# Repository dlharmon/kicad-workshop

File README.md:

# kicad-workshop
Material for a Kicad workshop

## Overview

A three session workshop on designing and assembling PCBs with
Kicad. A small group of students will design and build a USB
widget. The instructor will provide the basic circuit and
guidance. Materials cost will be approximately $20 including PCB
fabrication, components, shipping and solder paste stencil. We will
place a shared order to reduce shipping costs.

## [Slides](https://raw.githubusercontent.com/dlharmon/kicad-workshop/master/slides/kicad-workshop.pdf)

## The device

- [Silicon Labs EFM32HG309 microcontroller](https://www.silabs.com/products/mcu/32-bit/efm32-happy-gecko), ARM Cortex M0+, 64 kiB flash, 8 kiB ram USB device interface. About $1.50.
 - Connector for [128x64 pixel OLED](https://www.aliexpress.com/item/32847040077.html?spm=a2g0s.9042311.0.0.6e644c4dlFzZIQ) Display is not included in the parts kit, order one yourself if you want it.
 - LEDs
 - rotary encoder with push switch
 - USB for power and communication, will provide Python code to communicate with it from a PC
 - This is about $3 in parts yet demonstrates quite a few things

## Prerequisites
 - Laptop with [Kicad 5.1.4](http://www.kicad.org/download/) 5.1.2 is probably OK. Last time we had a few students using 5.0.x and it was problematic.
 - [Interactive HTML BOM plugin installed](https://github.com/openscopeproject/InteractiveHtmlBom) (optional, may require installing python3-wxgtk4)
 - Electronics knowledge is not required, but helpful.
 - Programming knowledge is not required, but helpful.
 - USB C cable (C-C for newer laptops, A-C for older) by last session. I'll have a few on hand.
 - Clone or download [https://github.com/sethhillbrand/kicad_templates.git](https://github.com/sethhillbrand/kicad_templates.git)

## Firmware
 - This is entirely optional. The instructor can flash firmware for you if you are not interested.
 - [ARM Cortex compiler](https://developer.arm.com/tools-and-software/open-source-software/developer-tools/gnu-toolchain/gnu-rm/downloads) Alternately, your Linux distro may have a package `gcc-arm-none-eabi` or similar which may work.
 - [OpenOCD](http://openocd.org/) required to flash the firmware the first time and until a bootloader is developed.
 - In the fw directory, `make flash` will build and flash the firmware. It assumes an FT232H based programmer with the default USB ID.
 - usb_comm.py can be used to interact with the device from Python over USB.

### udev rules

On Linux, to avoid having to run as root (change dlharmon to your user), add the following to `/etc/udev/rules.d/99-local.rules`:

```
ATTR{idVendor}=="0403", ATTR{idProduct}=="6014", SYMLINK+="ftdi-%k", MODE="660", GROUP="dlharmon"
SUBSYSTEM=="usb", ATTR{idVendor}=="10c4", ATTR{idProduct}=="8b00", MODE="0660", GROUP="dlharmon"
```

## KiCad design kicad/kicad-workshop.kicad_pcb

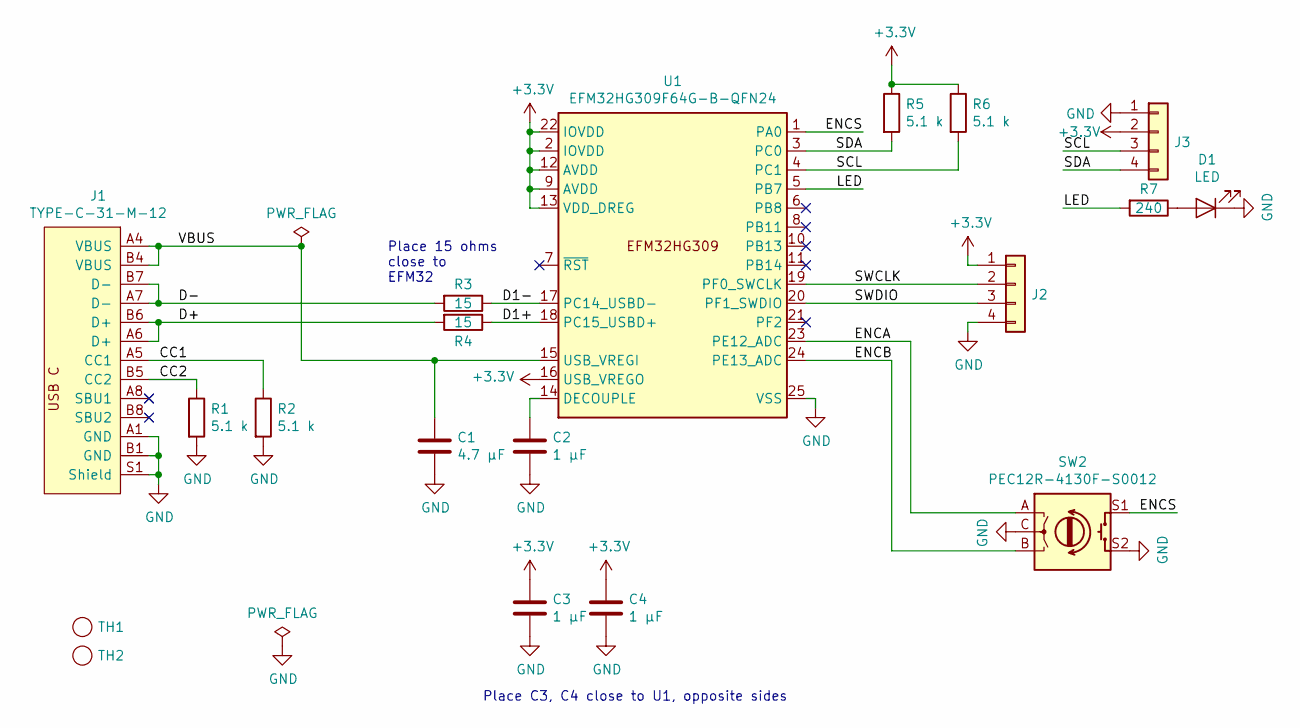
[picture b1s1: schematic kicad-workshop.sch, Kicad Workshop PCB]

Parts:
C1: 4.7 μF; C_0603_1608Metric
C2, C3, C4: 1 μF; C_0603_1608Metric
D1: LED; LED_0603_1608Metric
J1: TYPE-C-31-M-12; USB_C_Receptacle_HRO_TYPE-C-31-M-12
J2: Conn_01x04; PinHeader_1x04_P2.54mm_Vertical
J3: Conn_01x04; PinSocket_1x04_P2.54mm_Vertical
R1, R2, R5, R6: 5.1 k; R_0603_1608Metric
R3, R4: 15; R_0603_1608Metric
R7: 240; R_0603_1608Metric
SW2: PEC12R-4130F-S0012; RotaryEncoder_Alps_EC12E-Switch_Vertical_H20mm
TH1, TH2: tooling_hole; tooling_hole_2.55
U1: EFM32HG309F64G-B-QFN24; QFN-24-1EP_5x5mm_P0.65mm_EP3.6x3.6mm

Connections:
+3V3: C3.1, C4.1, J2.1, J3.2, R5.1, R6.1, U1.2 (IOVDD), U1.9 (AVDD), U1.12 (AVDD), U1.13 (VDD_DREG), U1.16 (USB_VREGO), U1.22 (IOVDD)
/CC1: J1.A5 (CC1), R2.1
/CC2: J1.B5 (CC2), R1.1
/D1+: R4.1, U1.18 (PC15_USBD+)
/D1-: R3.1, U1.17 (PC14_USBD-)
/D+: J1.A6 (D+), J1.B6 (D+), R4.2
/D-: J1.A7 (D-), J1.B7 (D-), R3.2
/ENCA: SW2.A, U1.23 (PE12_ADC)
/ENCB: SW2.B, U1.24 (PE13_ADC)
/ENCS: SW2.S1, U1.1 (PA0)
/LED: R7.2, U1.5 (PB7)
/SCL: J3.3, R6.2, U1.4 (PC1)
/SDA: J3.4, R5.2, U1.3 (PC0)
/SWCLK: J2.2, U1.19 (PF0_SWCLK)
/SWDIO: J2.3, U1.20 (PF1_SWDIO)
/VBUS: C1.1, J1.A4 (VBUS), J1.B4 (VBUS), U1.15 (USB_VREGI)
GND: C1.2, C2.2, C3.2, C4.2, D1.1 (K), J1.A1 (GND), J1.B1 (GND), J1.S1 (Shield), J2.4, J3.1, R1.2, R2.2, SW2.C, SW2.S2, U1.25 (VSS)
unnamed: C2.1, U1.14 (DECOUPLE)
unnamed: D1.2 (A), R7.1

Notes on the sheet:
Place 15 ohms close to EFM32
Place C3, C4 close to U1, opposite sides

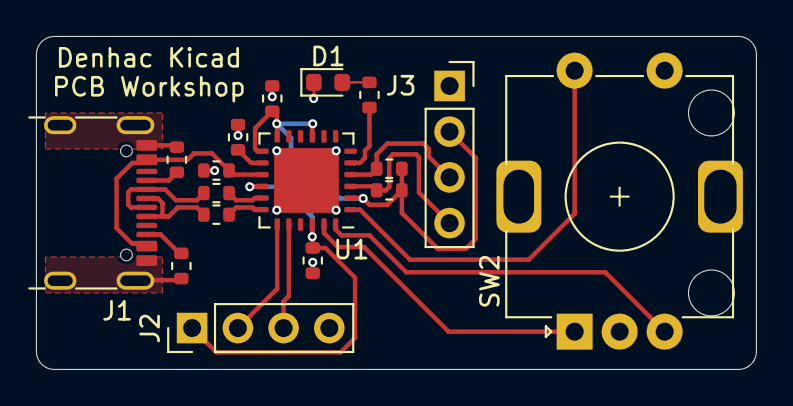
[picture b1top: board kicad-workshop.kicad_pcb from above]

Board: 2 copper layers, 40.0 x 18.5 mm, 19 parts (0 on the bottom side), 19 nets.

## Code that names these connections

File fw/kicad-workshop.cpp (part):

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#include <stdlib.h>
#include "font.h"

// R: PB7 TIM1 CC0
// G: PB8 TIM1 CC1
// B: PB11 TIM1 CC2

// ENCS: PA0 - pullup, act low
// ENCA: PE12 TIM2_CC2
// ENCB: PE13 TIM2_CC3
// SDA: PC0
// SCL: PC1
// USB: PC14, 15

#define SCL_PORT GPIOC // I2C0 AF4
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        // configure GPIOs

        // RGB LED
        // R: PB7 TIM1 CC0
        // G: PB8 TIM1 CC1
        // B: PB11 TIM1 CC2
        gpio_mode_setup(GPIOB, GPIO_MODE_PUSH_PULL, GPIO7 | GPIO8 | GPIO11);

        // ENCA: PE12 TIM2_CC2
        // ENCB: PE13 TIM2_CC3
        // ENCS: PA0 - pullup, act low
        gpio_mode_setup(GPIOE, GPIO_MODE_INPUT_PULL_FILTER, GPIO12 | GPIO13);
        GPIO_P_DOUTSET(GPIOE) = GPIO12 | GPIO13;
        gpio_mode_setup(INT_PORT, GPIO_MODE_INPUT_PULL_FILTER, INT_PIN);
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
        TIMER1_CMD = 1;

        GPIO_EXTIPSELL = 0;       // PA0 as ext interrupt
        GPIO_EXTIFALL = (1 << 0); // falling
        GPIO_EXTIRISE = (1 << 0); // rising
        GPIO_IEN = (1 << 0);
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
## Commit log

2019-07-14 add libraries and example of completed PCB
2019-07-14 remove .bak file, ignore
2019-08-16 initial quick and dirty microcontroller code
2019-08-16 update gitignore
2019-08-16 reduce solder paste on USB C
2019-08-17 Slides WIP
2019-08-17 add some images to slides
2019-08-17 add libs not present on some machines
2019-09-14 add udev note
2019-09-14 fix readme
2019-09-14 update firmware
2019-09-26 add note about HTML BOM dependency
2019-11-01 use pid.codes USB ID http://pid.codes/1209/F00F/
2019-11-01 update readme - LED, Kicad version
2019-11-09 change LED to single color The 1x1 mm LED was too difficult for assembly, mostly locating pin 1
2019-11-09 reduce solder paste volume on USB C
2019-11-17 add template link
2019-12-11 change LED GPIO to push pull for later boards
2021-10-19 update kicad link
